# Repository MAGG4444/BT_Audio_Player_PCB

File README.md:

# BT_Audio_Player_PCB
Bluetooth-enabled audio player PCB for wireless audio playback and easy device integration.

- This design is a Bluetooth speaker control board built around an RP2350 microcontroller, a BM83 Bluetooth audio module, and a MAX98357A digital audio amplifier. The BM83 handles Bluetooth pairing and wireless audio reception, the RP2350 manages system control and external interfaces, and the MAX98357A drives the speaker output. Supporting parts include a W25Q128 external flash for storage, an NCP1117-3.3 regulator for power, USB-C input with ESD protection, status LEDs, reset and boot buttons, debug and expansion headers, and speaker or microphone connectors. Overall, the board is intended to receive audio over Bluetooth, process and control it through the MCU, and output sound to a speaker in a compact, product-ready hardware design.

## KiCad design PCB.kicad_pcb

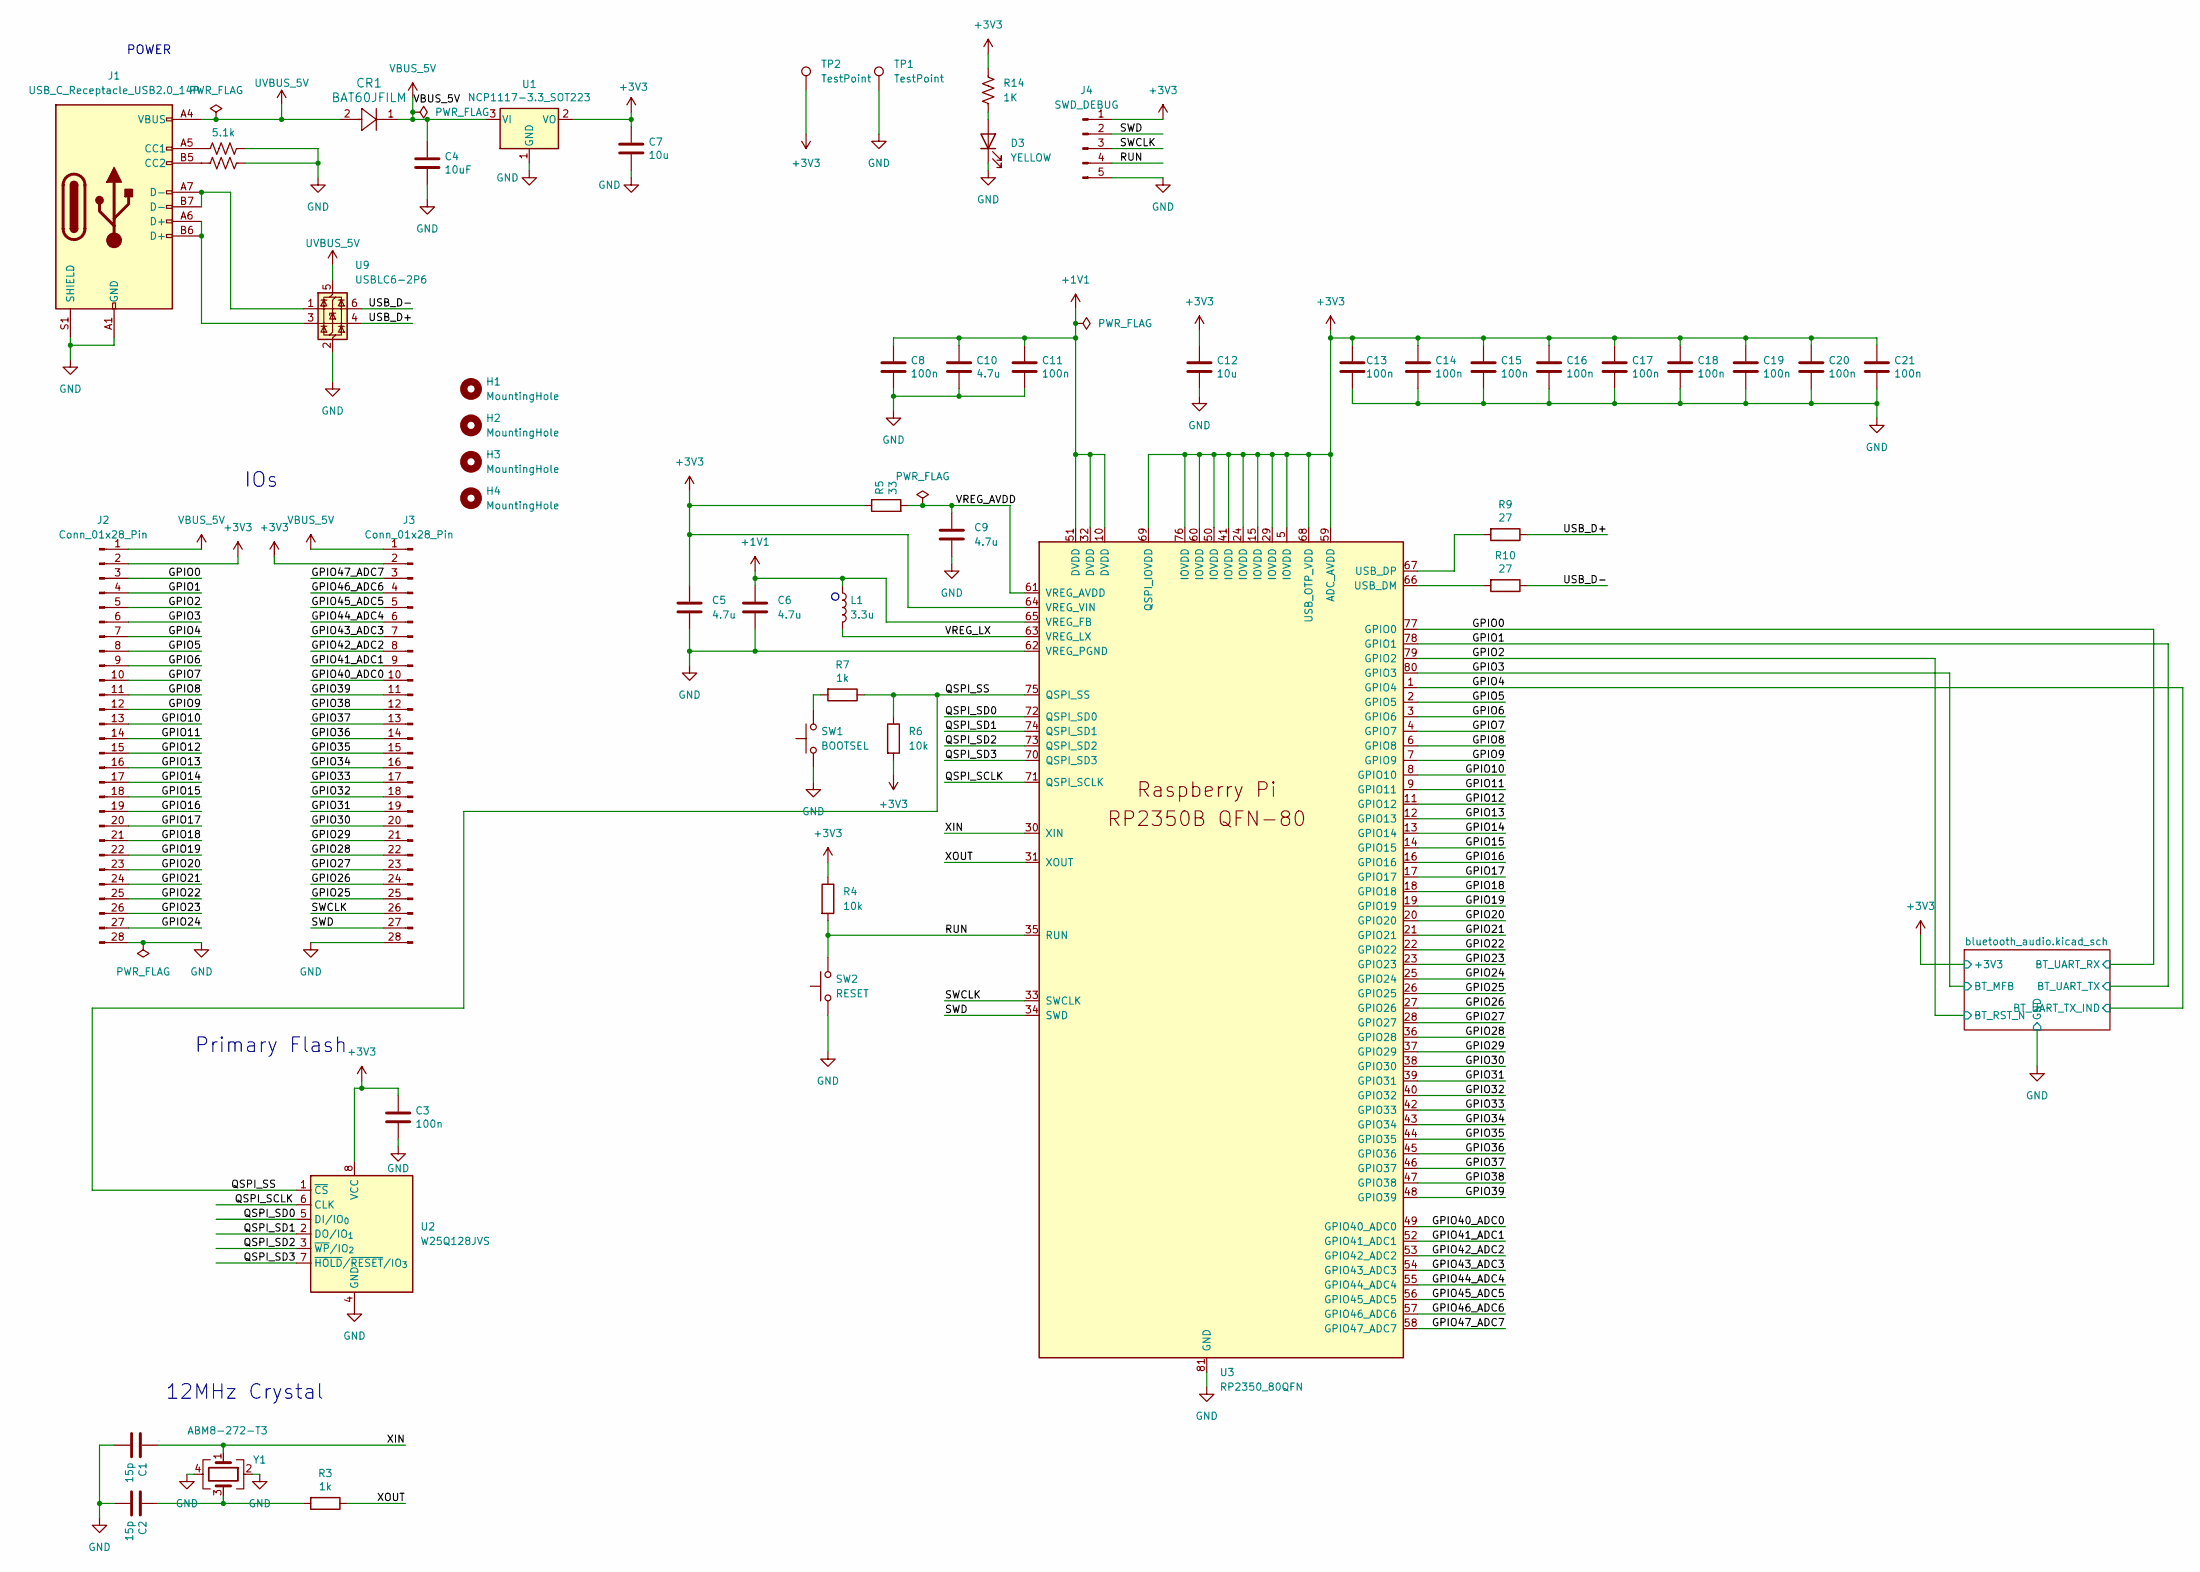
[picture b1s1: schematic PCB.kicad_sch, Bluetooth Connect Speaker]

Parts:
C1, C2: 15p; C_0402_1005Metric
C3, C8, C11, C13, C14, C15, C16, C17, C18, C19, C20, C21: 100n; C_0402_1005Metric
C4: 10uF; C_0805_2012Metric
C5, C6, C9, C10: 4.7u; C_0402_1005Metric
C7, C12: 10u; C_0805_2012Metric
CR1: BAT60JFILM; CR_60JFILM_STM
D3: YELLOW; LED_0805_2012Metric
H1, H2, H3, H4: MountingHole; MountingHole_2.2mm_M2
J1: USB_C_Receptacle_USB2.0_14P; USB_C_Receptacle_G-Switch_GT-USB-7010ASV
J2, J3: Conn_01x28_Pin; PinHeader_1x28_P2.54mm_Vertical
J4: SWD_DEBUG; PinHeader_1x05_P2.54mm_Vertical
L1: 3.3u; L_0402_1005Metric
R1, R2: 5.1k; R_0402_1005Metric
R3, R7: 1k; R_0402_1005Metric
R4: 10k; R_0805_2012Metric
R5: 33; R_0402_1005Metric
R6: 10k; R_0402_1005Metric
R9, R10: 27; R_0402_1005Metric
R14: 1K; R_0805_2012Metric
SW1: BOOTSEL; SW_SPST_PTS647_Sx38
SW2: RESET; SW_SPST_PTS647_Sx38
TP1, TP2: TestPoint; TestPoint_Pad_D1.5mm
U1: NCP1117-3.3_SOT223; SOT-223-3_TabPin2
U2: W25Q128JVS; SOIC-8_5.3x5.3mm_P1.27mm
U3: RP2350_80QFN; QFN-80-1EP_10x10mm_P0.4mm_EP3.4x3.4mm
U9: USBLC6-2P6; SOT-666
Y1: ABM8-272-T3; Crystal_SMD_3225-4Pin_3.2x2.5mm

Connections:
+1V1: C6.1, C8.1, C10.1, C11.1, L1.1, U3.10 (DVDD), U3.32 (DVDD), U3.51 (DVDD), U3.65 (VREG_FB)
+3V3: C3.1, C5.1, C7.1, C12.1, C13.1, C14.1, C15.1, C16.1, C17.1, C18.1, C19.1, C20.1, C21.1, J2.2, J3.2, J4.1, R4.1, R5.1, R6.2, R14.1, TP2.1, U1.2 (VO), U2.8 (VCC), U3.5 (IOVDD), U3.15 (IOVDD), U3.24 (IOVDD), U3.29 (IOVDD), U3.41 (IOVDD), U3.50 (IOVDD), U3.59 (ADC_AVDD), U3.60 (IOVDD), U3.64 (VREG_VIN), U3.68 (USB_OTP_VDD), U3.69 (QSPI_IOVDD), U3.76 (IOVDD); also elsewhere on the board
/GPIO0: J2.3, U3.77 (GPIO0); also elsewhere on the board
/GPIO1: J2.4, U3.78 (GPIO1); also elsewhere on the board
/GPIO2: J2.5, U3.79 (GPIO2); also elsewhere on the board
/GPIO3: J2.6, U3.80 (GPIO3); also elsewhere on the board
/GPIO4: J2.7, U3.1 (GPIO4); also elsewhere on the board
/GPIO5: J2.8, U3.2 (GPIO5)
/GPIO6: J2.9, U3.3 (GPIO6)
/GPIO7: J2.10, U3.4 (GPIO7)
/GPIO8: J2.11, U3.6 (GPIO8)
/GPIO9: J2.12, U3.7 (GPIO9)
/GPIO10: J2.13, U3.8 (GPIO10)
/GPIO11: J2.14, U3.9 (GPIO11)
/GPIO12: J2.15, U3.11 (GPIO12)
/GPIO13: J2.16, U3.12 (GPIO13)
/GPIO14: J2.17, U3.13 (GPIO14)
/GPIO15: J2.18, U3.14 (GPIO15)
/GPIO16: J2.19, U3.16 (GPIO16)
/GPIO17: J2.20, U3.17 (GPIO17)
/GPIO18: J2.21, U3.18 (GPIO18)
/GPIO19: J2.22, U3.19 (GPIO19)
/GPIO20: J2.23, U3.20 (GPIO20)
/GPIO21: J2.24, U3.21 (GPIO21)
/GPIO22: J2.25, U3.22 (GPIO22)
/GPIO23: J2.26, U3.23 (GPIO23)
/GPIO24: J2.27, U3.25 (GPIO24)
/GPIO25: J3.25, U3.26 (GPIO25)
/GPIO26: J3.24, U3.27 (GPIO26)
/GPIO27: J3.23, U3.28 (GPIO27)
/GPIO28: J3.22, U3.36 (GPIO28)
/GPIO29: J3.21, U3.37 (GPIO29)
/GPIO30: J3.20, U3.38 (GPIO30)
/GPIO31: J3.19, U3.39 (GPIO31)
/GPIO32: J3.18, U3.40 (GPIO32)
/GPIO33: J3.17, U3.42 (GPIO33)
/GPIO34: J3.16, U3.43 (GPIO34)
/GPIO35: J3.15, U3.44 (GPIO35)
/GPIO36: J3.14, U3.45 (GPIO36)
/GPIO37: J3.13, U3.46 (GPIO37)
/GPIO38: J3.12, U3.47 (GPIO38)
/GPIO39: J3.11, U3.48 (GPIO39)
/GPIO40_ADC0: J3.10, U3.49 (GPIO40_ADC0)
/GPIO41_ADC1: J3.9, U3.52 (GPIO41_ADC1)
/GPIO42_ADC2: J3.8, U3.53 (GPIO42_ADC2)
/GPIO43_ADC3: J3.7, U3.54 (GPIO43_ADC3)
/GPIO44_ADC4: J3.6, U3.55 (GPIO44_ADC4)
/GPIO45_ADC5: J3.5, U3.56 (GPIO45_ADC5)
/GPIO46_ADC6: J3.4, U3.57 (GPIO46_ADC6)
/GPIO47_ADC7: J3.3, U3.58 (GPIO47_ADC7)
/QSPI_SCLK: U2.6 (CLK), U3.71 (QSPI_SCLK)
/QSPI_SD0: U2.5 (DI/IO_{0}), U3.72 (QSPI_SD0)
/QSPI_SD1: U2.2 (DO/IO_{1}), U3.74 (QSPI_SD1)
/QSPI_SD2: U2.3 (~WP/IO_{2}), U3.73 (QSPI_SD2)
/QSPI_SD3: U2.7 (~HOLD/~RESET/IO_{3}), U3.70 (QSPI_SD3)
/QSPI_SS: R6.1, R7.1, U2.1 (~CS), U3.75 (QSPI_SS)
/RUN: J4.4, R4.2, SW2.2, U3.35 (RUN)
/SWCLK: J3.26, J4.3, U3.33 (SWCLK)
/SWD: J3.27, J4.2, U3.34 (SWD)
/USB_D+: R9.1, U9.4 (I/O2)
/USB_D-: R10.1, U9.6 (I/O1)
/VREG_AVDD: C9.1, R5.2, U3.61 (VREG_AVDD)
/VREG_LX: L1.2, U3.63 (VREG_LX)
/XIN: C1.1, U3.30 (XIN), Y1.1
/XOUT: R3.1, U3.31 (XOUT)
GND: C1.2, C2.2, C3.2, C4.2, C5.2, C6.2, C7.2, C8.2, C9.2, C10.2, C11.2, C12.2, C13.2, C14.2, C15.2, C16.2, C17.2, C18.2, C19.2, C20.2, C21.2, D3.1 (K), J1.A1 (GND), J1.A12 (GND), J1.B1 (GND), J1.B12 (GND), J1.S1 (SHIELD), J2.28, J3.28, J4.5, R1.2, R2.2, SW1.1, SW2.1, TP1.1, U1.1 (GND), U2.4 (GND), U3.62 (VREG_PGND), U3.81 (GND), U9.2 (GND), Y1.2, Y1.4; also elsewhere on the board
unnamed: C2.1, R3.2, Y1.3
unnamed: D3.2 (A), R14.2
unnamed: J1.A5 (CC1), R1.1
unnamed: J1.B5 (CC2), R2.1
unnamed: J1.A6 (D+), J1.B6 (D+), U9.3 (I/O2)
unnamed: J1.A7 (D-), J1.B7 (D-), U9.1 (I/O1)
unnamed: R7.2, SW1.2
unnamed: R10.2, U3.66 (USB_DM)
unnamed: R9.2, U3.67 (USB_DP)
UVBUS_5V: CR1.2, J1.A4 (VBUS), J1.A9 (VBUS), J1.B4 (VBUS), J1.B9 (VBUS), U9.5 (VBUS)
VBUS_5V: C4.1, CR1.1, J2.1, J3.1, U1.3 (VI)

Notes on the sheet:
IOs
Primary Flash
12MHz Crystal
POWER

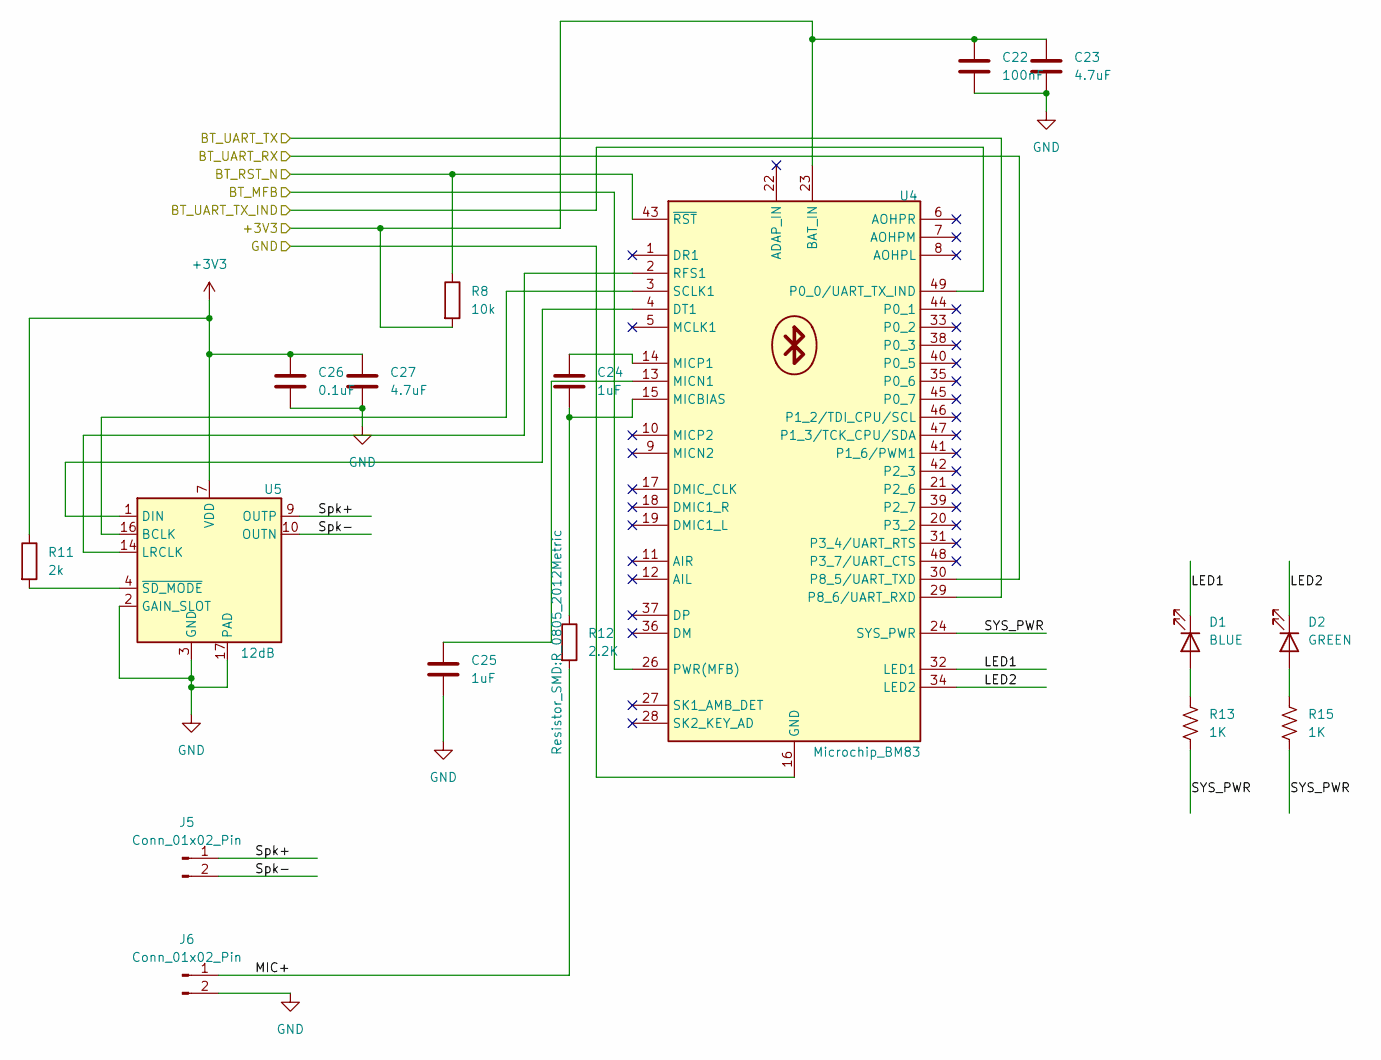
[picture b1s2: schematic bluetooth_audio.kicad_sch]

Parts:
C22: 100nF; C_0402_1005Metric
C23, C27: 4.7uF; C_0402_1005Metric
C24, C25: 1uF; C_0402_1005Metric
C26: 0.1uF; C_0402_1005Metric
D1: BLUE; LED_0805_2012Metric
D2: GREEN; LED_0805_2012Metric
J5, J6: Conn_01x02_Pin; PinHeader_1x02_P2.54mm_Vertical
R8: 10k; R_0805_2012Metric
R11: 2k; R_0805_2012Metric
R12: 2.2K; R_0805_2012Metric
R13, R15: 1K; R_0402_1005Metric
U4: Microchip_BM83
U5: 12dB; TQFN-16-1EP_3x3mm_P0.5mm_EP1.23x1.23mm

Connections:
+3V3: C22.1, C23.1, C26.1, C27.1, R8.2, R11.1, U4.23 (BAT_IN), U5.7 (VDD), U5.8 (VDD); also elsewhere on the board
/GPIO0: U4.30 (P8_5/UART_TXD); also elsewhere on the board
/GPIO1: U4.29 (P8_6/UART_RXD); also elsewhere on the board
/GPIO2: R8.1, U4.43 (~RST); also elsewhere on the board
/GPIO3: U4.26 (PWR(MFB)); also elsewhere on the board
/GPIO4: U4.49 (P0_0/UART_TX_IND); also elsewhere on the board
/bluetooth_audio.kicad_sch/LED1: D1.1 (K), U4.32 (LED1)
/bluetooth_audio.kicad_sch/LED2: D2.1 (K), U4.34 (LED2)
/bluetooth_audio.kicad_sch/MIC+: J6.1, R12.2; also elsewhere on the board
/bluetooth_audio.kicad_sch/SYS_PWR: R13.2, R15.2, U4.24 (SYS_PWR)
/bluetooth_audio.kicad_sch/Spk+: J5.1, U5.9 (OUTP)
/bluetooth_audio.kicad_sch/Spk-: J5.2, U5.10 (OUTN)
GND: C22.2, C23.2, C25.2, C26.2, C27.2, J6.2, U4.16 (GND), U4.50 (GND), U4.56 (GND), U4.57 (GND), U5.2 (GAIN_SLOT), U5.3 (GND), U5.11 (GND), U5.15 (GND), U5.17 (PAD); also elsewhere on the board
unnamed: D1.2 (A), R13.1
unnamed: D2.2 (A), R15.1
unnamed: U4.4 (DT1), U5.1 (DIN)
unnamed: C24.2, R12.1, U4.15 (MICBIAS)
unnamed: C25.1, U4.13 (MICN1)
unnamed: C24.1, U4.14 (MICP1)
unnamed 87: U4.2 (RFS1), U5.14 (LRCLK); also elsewhere on the board
unnamed: U4.3 (SCLK1), U5.16 (BCLK)
unnamed: R11.2, U5.4 (~SD_MODE)

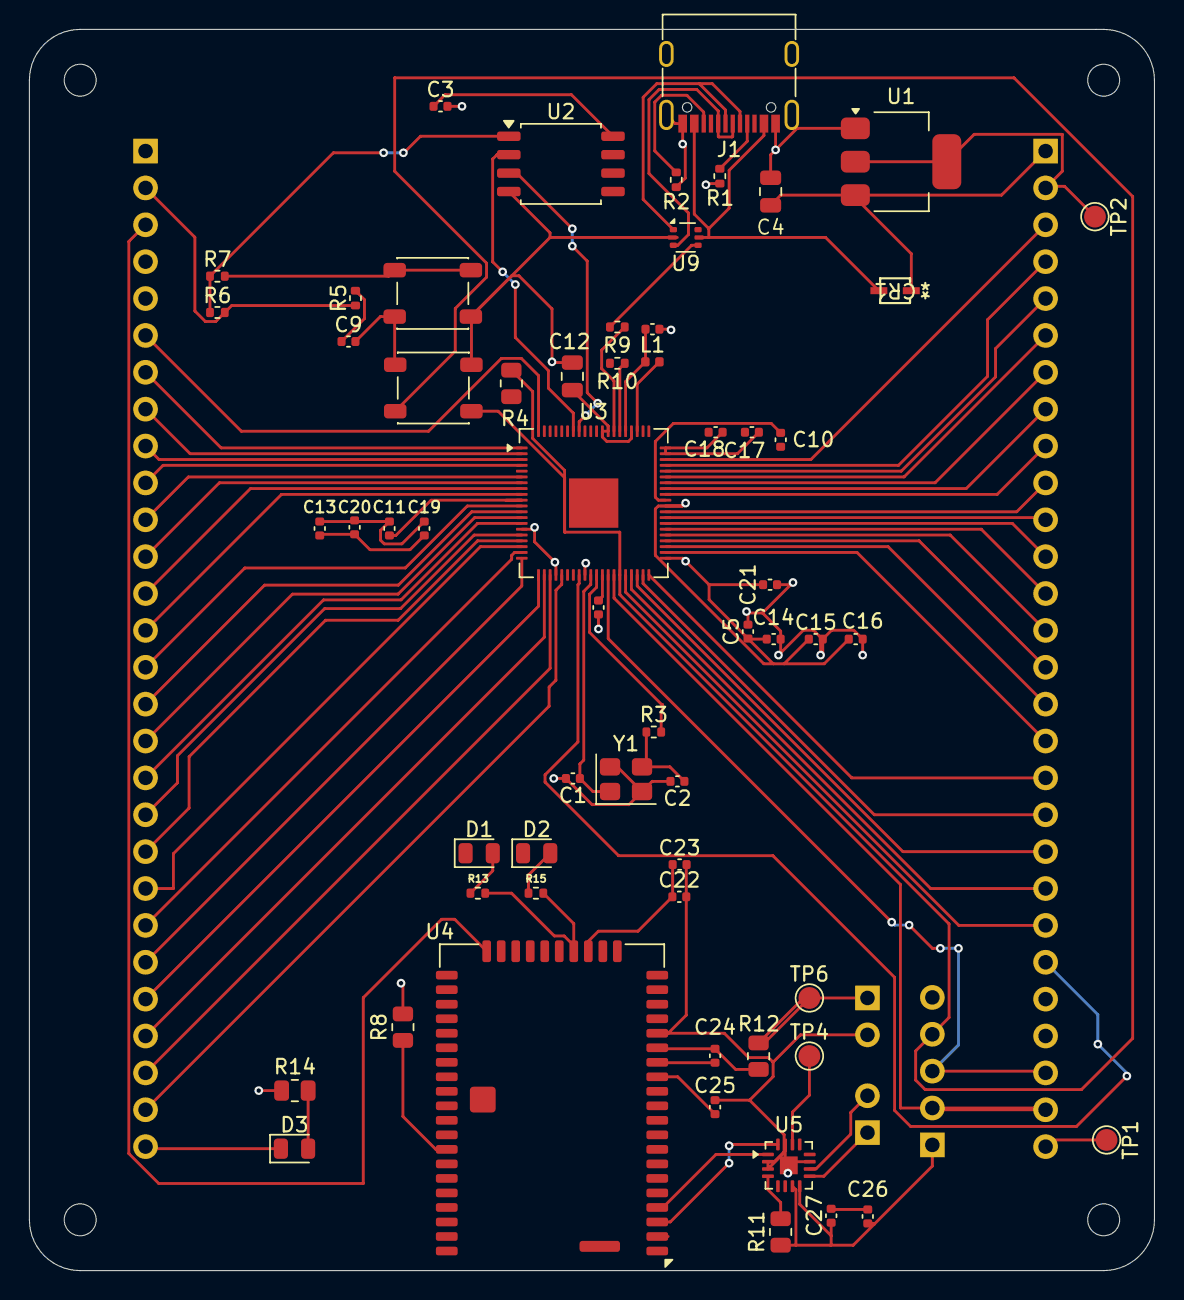
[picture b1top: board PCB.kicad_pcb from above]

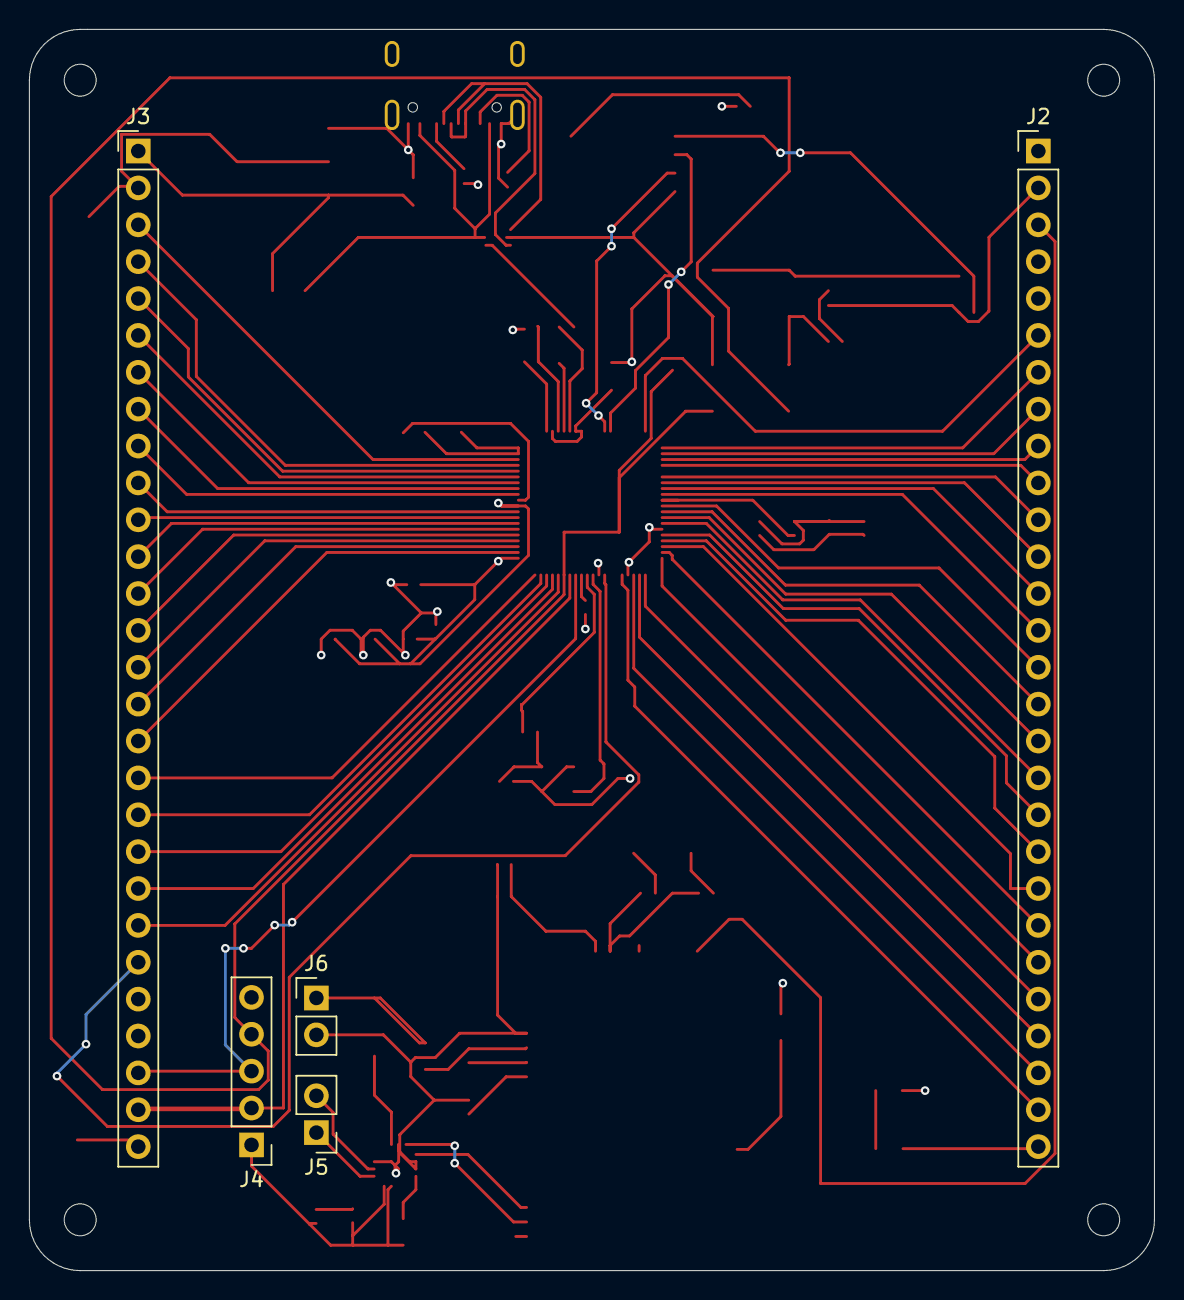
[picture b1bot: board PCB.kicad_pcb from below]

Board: 2 copper layers, 77.5 x 85.5 mm, 69 parts (5 on the bottom side), 92 nets.

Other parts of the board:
TP4, TP6: TestPoint; TestPoint_Pad_D1.5mm

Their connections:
/bluetooth_audio.kicad_sch/MIC+: TP6.1; also elsewhere on the board
unnamed 87: TP4.1; also elsewhere on the board

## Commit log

2026-04-05 Enhance README with project overview
    Added a brief overview of the PCB design and its components.
